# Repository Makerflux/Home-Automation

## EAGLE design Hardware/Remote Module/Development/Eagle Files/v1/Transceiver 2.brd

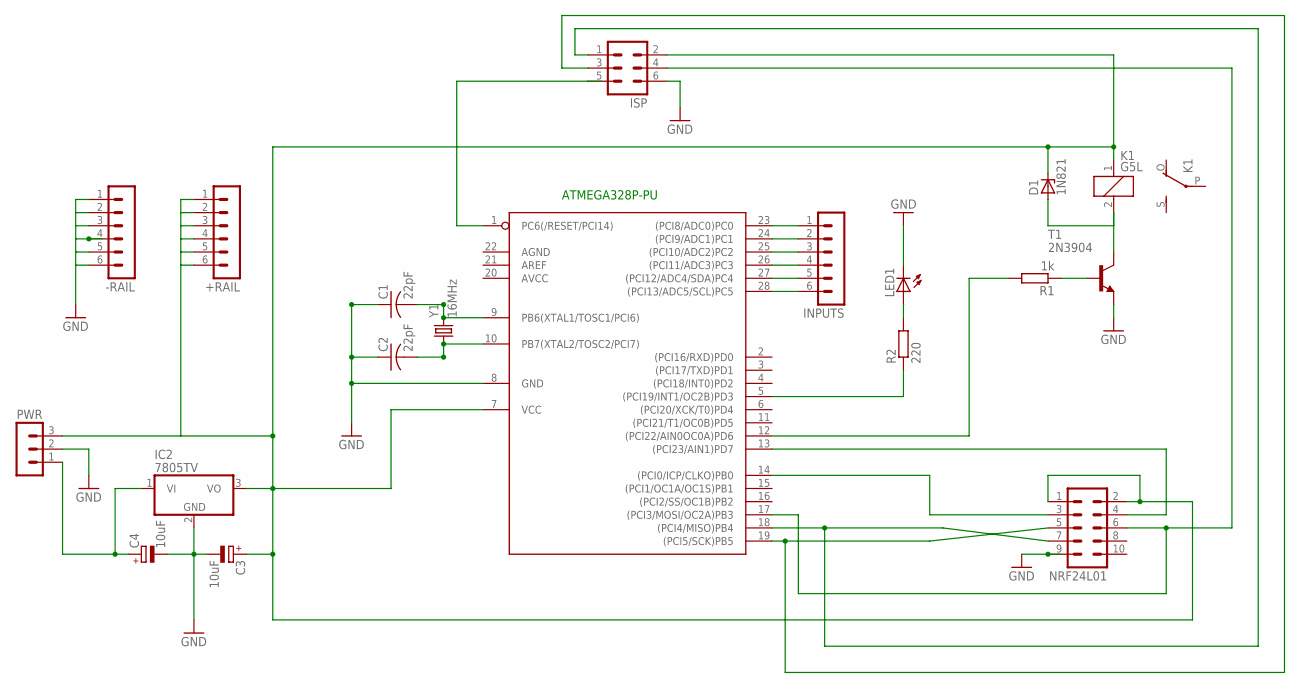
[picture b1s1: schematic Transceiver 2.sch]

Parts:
+RAIL: MA06-1
-RAIL: MA06-1
C1, C2: 22pF; C025-024X044
C3, C4: 10uF; E2-5
D1: 1N821; DO35Z10
IC1: ATMEGA168-20P; DIL28-3
IC2: 7805TV; TO220V
INPUTS: MA06-1
ISP: MA03-2
K1: G5L; G5LE
LED1: LED3MM
NRF24L01: MA05-2
PWR: MA03-1
R1: 1k; 0204/7
R2: 220; 0204/7
T1: 2N3904; TO92
Y1: 16MHz; HC49US

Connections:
5VRAIL: +RAIL.1, +RAIL.2, +RAIL.3, +RAIL.4, +RAIL.5, +RAIL.6, C3.+, D1.C, IC1.7 (VCC), IC2.3 (VO), ISP.2, K1.1, NRF24L01.1, NRF24L01.2, PWR.3
GND: -RAIL.1, -RAIL.2, -RAIL.3, -RAIL.4, -RAIL.5, -RAIL.6, C1.1, C2.1, C3.-, C4.-, IC1.8 (GND), IC2.2 (GND), ISP.6, LED1.K (C), NRF24L01.9, PWR.2, T1.3 (E)
unnamed: IC1.14 ((PCI0/ICP/CLKO)PB0), NRF24L01.3
unnamed: C1.2, IC1.9 (PB6(XTAL1/TOSC1/PCI6)), Y1.2
unnamed: C2.2, IC1.10 (PB7(XTAL2/TOSC2/PCI7)), Y1.1
unnamed: IC1.19 ((PCI5/SCK)PB5), ISP.3, NRF24L01.5
unnamed: IC1.13 ((PCI23/AIN1)PD7), NRF24L01.4
unnamed: IC1.17 ((PCI3/MOSI/OC2A)PB3), ISP.4, NRF24L01.6
unnamed: C4.+, IC2.1 (VI), PWR.1
unnamed: IC1.12 ((PCI22/AIN0OC0A)PD6), R1.2
unnamed: IC1.5 ((PCI19/INT1/OC2B)PD3), R2.1
unnamed: LED1.A, R2.2
unnamed: IC1.1 (PC6(/RESET/PCI14)), ISP.5
unnamed: D1.A, K1.2, T1.1 (C)
unnamed: R1.1, T1.2 (B)
unnamed: IC1.28 ((PCI13/ADC5/SCL)PC5), INPUTS.6
unnamed: IC1.27 ((PCI12/ADC4/SDA)PC4), INPUTS.5
unnamed: IC1.18 ((PCI4/MISO)PB4), ISP.1, NRF24L01.7
unnamed: IC1.23 ((PCI8/ADC0)PC0), INPUTS.1
unnamed: IC1.24 ((PCI9/ADC1)PC1), INPUTS.2
unnamed: IC1.25 ((PCI10/ADC2)PC2), INPUTS.3
unnamed: IC1.26 ((PCI11/ADC3)PC3), INPUTS.4

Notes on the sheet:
ATMEGA328P-PU

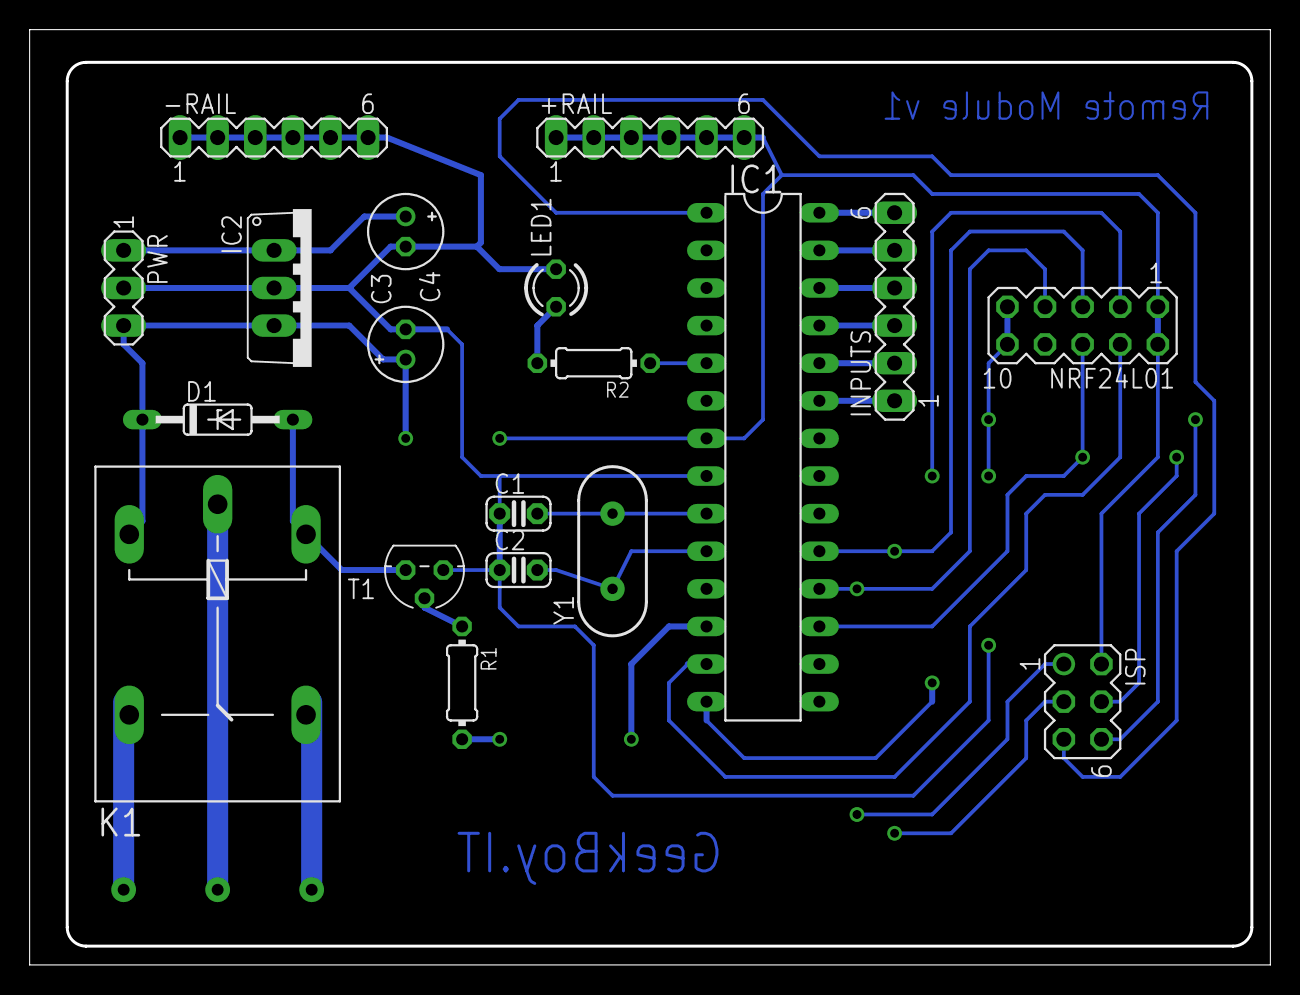
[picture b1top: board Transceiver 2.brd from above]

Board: 2 copper layers, 83.6 x 63.0 mm, 19 parts (0 on the bottom side), 22 nets.

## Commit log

2012-12-20 Project Creation
2012-12-21 Added g-code and firmware
2013-01-14 Added Eagle files for remote module
